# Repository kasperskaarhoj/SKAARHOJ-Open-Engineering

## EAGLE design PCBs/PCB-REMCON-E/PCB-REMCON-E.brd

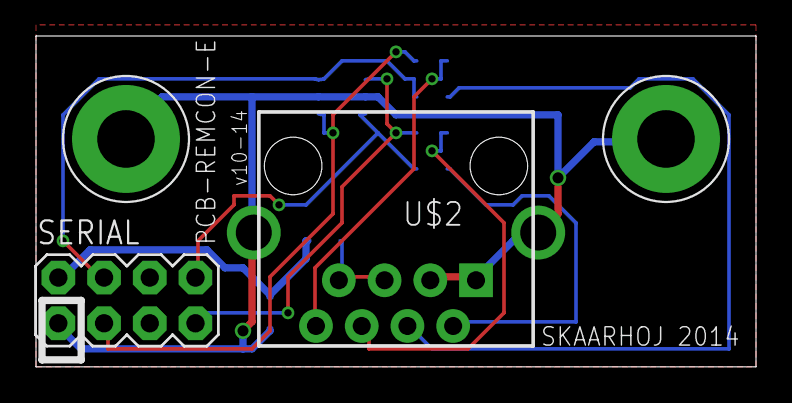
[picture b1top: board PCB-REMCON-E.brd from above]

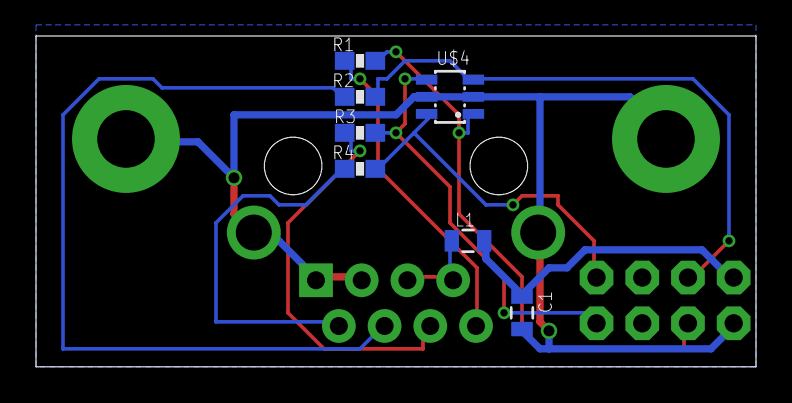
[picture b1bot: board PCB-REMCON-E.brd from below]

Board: 2 copper layers, 40.0 x 18.4 mm, 11 parts (7 on the bottom side), 11 nets.

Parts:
C1: 22uF; 0805
L1: 0805
R1, R2, R3, R4: 50R; 0603-RES
SERIAL: M04X2; 2X4
U$2: RJ45-8_GND
U$3, U$20: GNDPAD6MM; 3.2MMPAD6MM
U$4: TVS_DIODE_ARRAY4; SOT23-6L

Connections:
5V: C1.1, L1.2, SERIAL.2
GND: C1.2, SERIAL.1, U$2.1, U$2.3, U$2.GND, U$2.GND1, U$3.P$1, U$4.2, U$4.5, U$20.P$1
I2C_SCL: R2.2, SERIAL.4, U$4.3
I2C_SCL_IN: R2.1, U$2.4
I2C_SDA: R1.2, SERIAL.3, U$4.1
I2C_SDA_IN: R1.1, U$2.8
unnamed: L1.1, U$2.5, U$2.7
SPI_MOSI: R4.2, SERIAL.8, U$4.6
SPI_MOSI_IN: R4.1, U$2.2
SPI_SCLK: R3.2, SERIAL.7, U$4.4
SPI_SCLK_IN: R3.1, U$2.6

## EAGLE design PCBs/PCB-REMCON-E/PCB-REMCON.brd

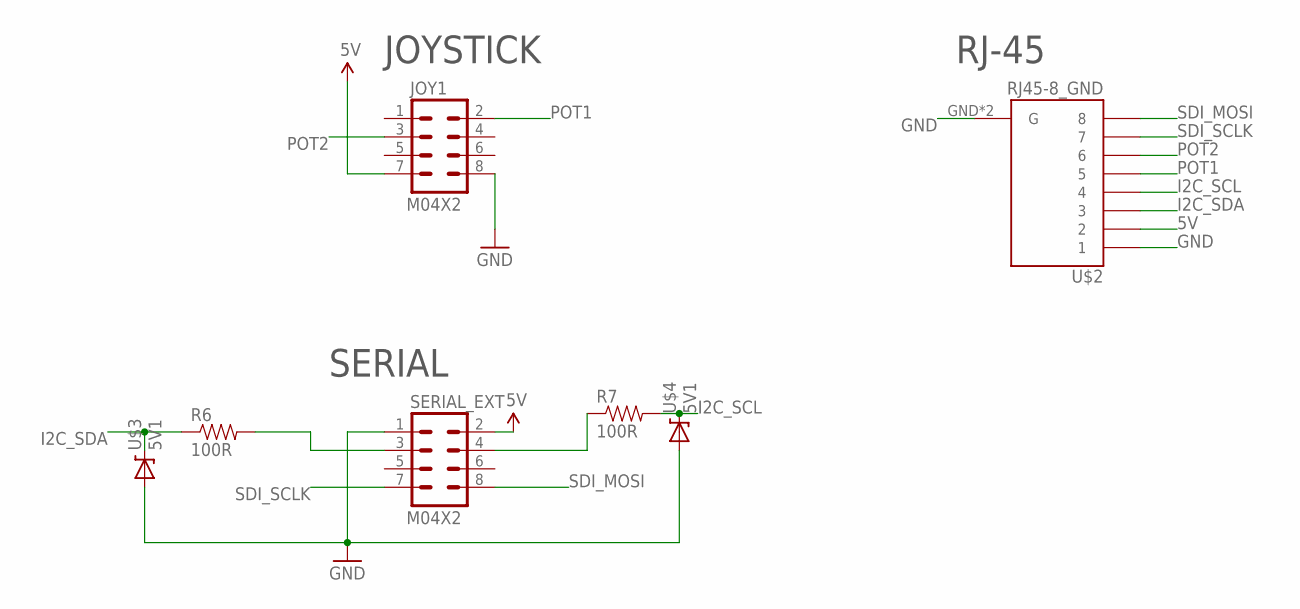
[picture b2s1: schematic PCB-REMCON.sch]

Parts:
JOY1: M04X2; 2X4
R6, R7: 100R; 0603-RES
SERIAL_EXT: M04X2; 2X4
U$2: RJ45-8_GND
U$3, U$4: 5V1; DIODE-ZENER

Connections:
5V: JOY1.7, SERIAL_EXT.2, U$2.2
GND: JOY1.8, SERIAL_EXT.1, U$2.1, U$2.GND (G), U$2.GND1 (G), U$3.P$2 (A), U$4.P$2 (A)
I2C_SCL: R7.2, U$2.4, U$4.P$1 (C)
I2C_SDA: R6.1, U$2.3, U$3.P$1 (C)
unnamed: R6.2, SERIAL_EXT.3
unnamed: R7.1, SERIAL_EXT.4
POT1: JOY1.2, U$2.5
POT2: JOY1.3, U$2.6
SDI_MOSI: SERIAL_EXT.8, U$2.8
SDI_SCLK: SERIAL_EXT.7, U$2.7

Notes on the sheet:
JOYSTICK
SERIAL
RJ-45

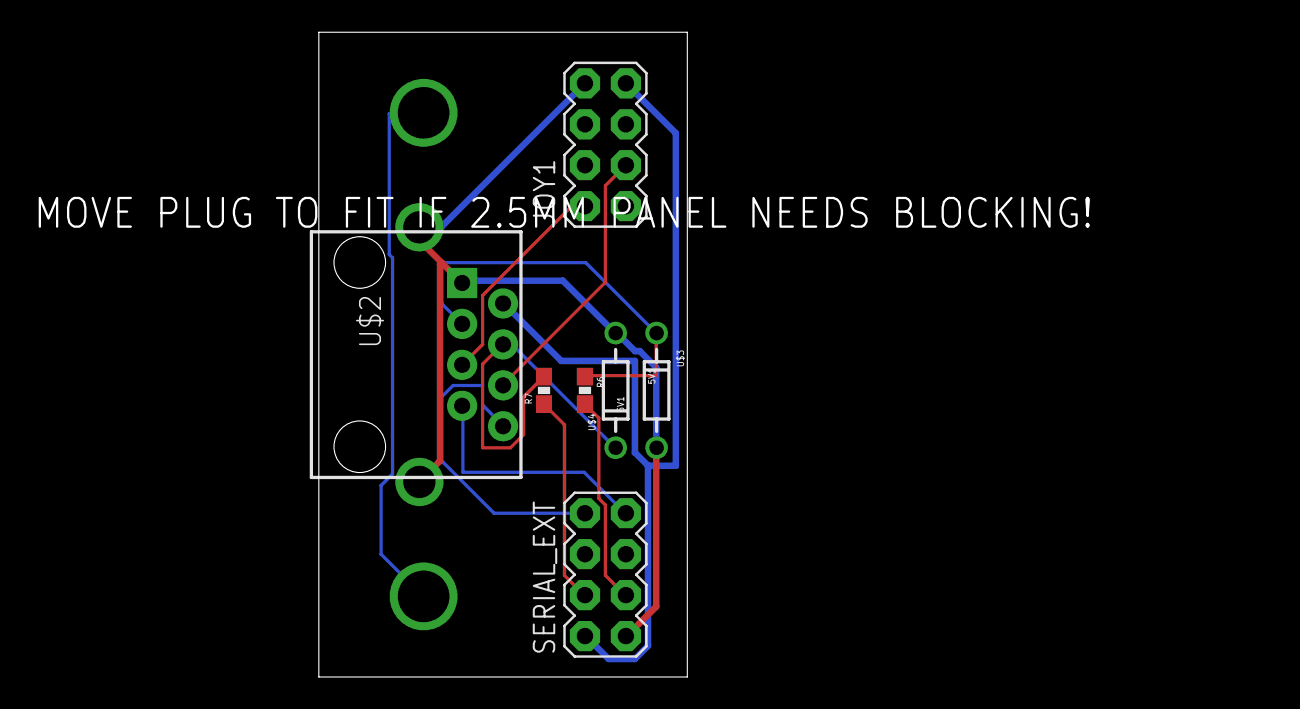
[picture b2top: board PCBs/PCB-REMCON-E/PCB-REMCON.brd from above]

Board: 2 copper layers, 22.9 x 40.0 mm, 7 parts (0 on the bottom side), 10 nets.

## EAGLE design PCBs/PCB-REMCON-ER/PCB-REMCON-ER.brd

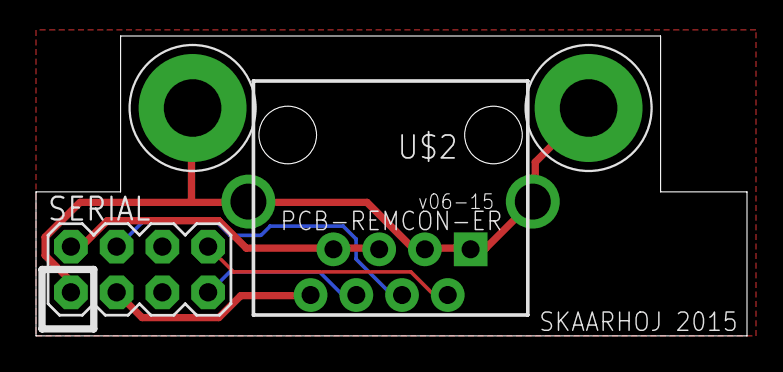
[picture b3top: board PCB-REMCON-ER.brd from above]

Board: 2 copper layers, 39.5 x 16.7 mm, 4 parts (0 on the bottom side), 6 nets.

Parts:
SERIAL: M04X2; 2X4
U$2: RJ45-8_GND
U$3, U$20: GNDPAD6MM; 3.2MMPAD6MM

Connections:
5V: SERIAL.2, U$2.5, U$2.7
GND: SERIAL.1, U$2.1, U$2.3, U$2.GND, U$2.GND1, U$3.P$1, U$20.P$1
I2C_SCL: SERIAL.4, U$2.4
I2C_SDA: SERIAL.3, U$2.8
SDI_MOSI: SERIAL.8, U$2.2
SDI_SCLK: SERIAL.7, U$2.6

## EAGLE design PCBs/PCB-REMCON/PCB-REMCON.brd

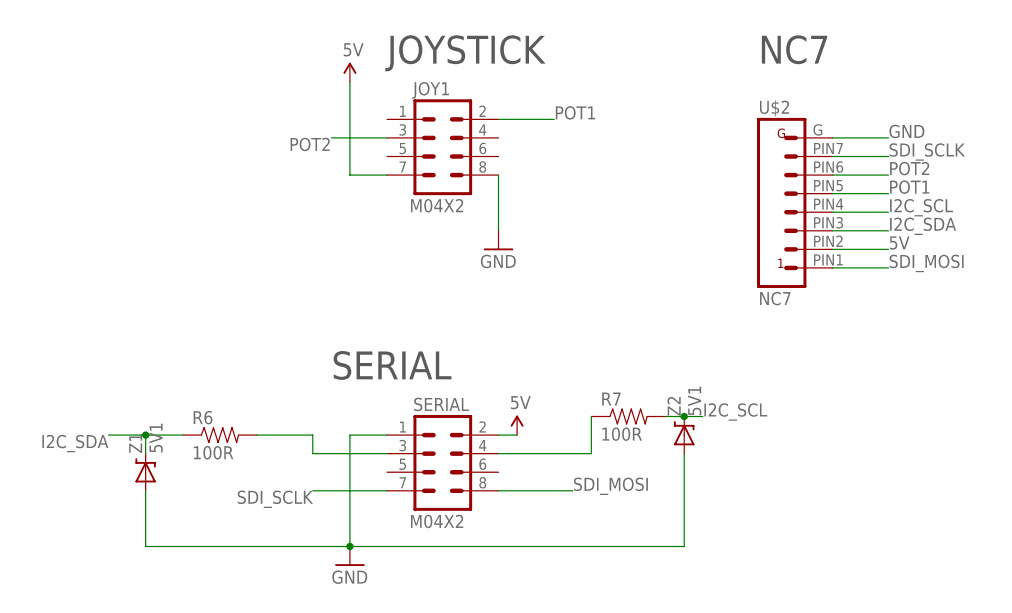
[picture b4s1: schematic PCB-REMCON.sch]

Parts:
JOY1: M04X2; 2X4
R6, R7: 100R; 0603-RES
SERIAL: M04X2; 2X4
U$2: NC7; NC7-MD-L1
Z1, Z2: 5V1; DIODE-ZENER

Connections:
5V: JOY1.7, SERIAL.2, U$2.PIN2 (2)
GND: JOY1.8, SERIAL.1, U$2.G, Z1.P$2 (A), Z2.P$2 (A)
I2C_SCL: R7.2, U$2.PIN4 (4), Z2.P$1 (C)
I2C_SDA: R6.1, U$2.PIN3 (3), Z1.P$1 (C)
unnamed: R6.2, SERIAL.3
unnamed: R7.1, SERIAL.4
POT1: JOY1.2, U$2.PIN5 (5)
POT2: JOY1.3, U$2.PIN6 (6)
SDI_MOSI: SERIAL.8, U$2.PIN1 (1)
SDI_SCLK: SERIAL.7, U$2.PIN7 (7)

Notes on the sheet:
NC7
JOYSTICK
SERIAL

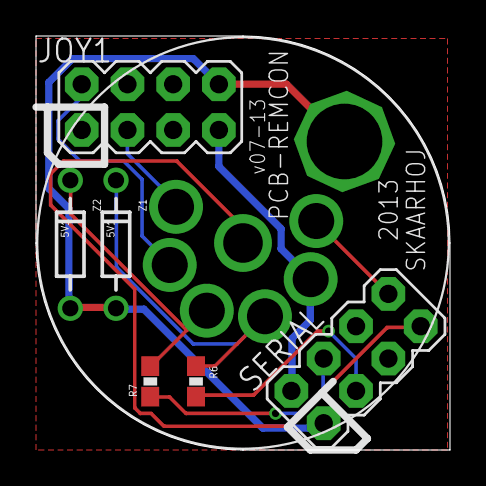
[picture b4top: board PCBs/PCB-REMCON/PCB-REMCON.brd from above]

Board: 2 copper layers, 23.0 x 23.0 mm, 7 parts (0 on the bottom side), 10 nets.

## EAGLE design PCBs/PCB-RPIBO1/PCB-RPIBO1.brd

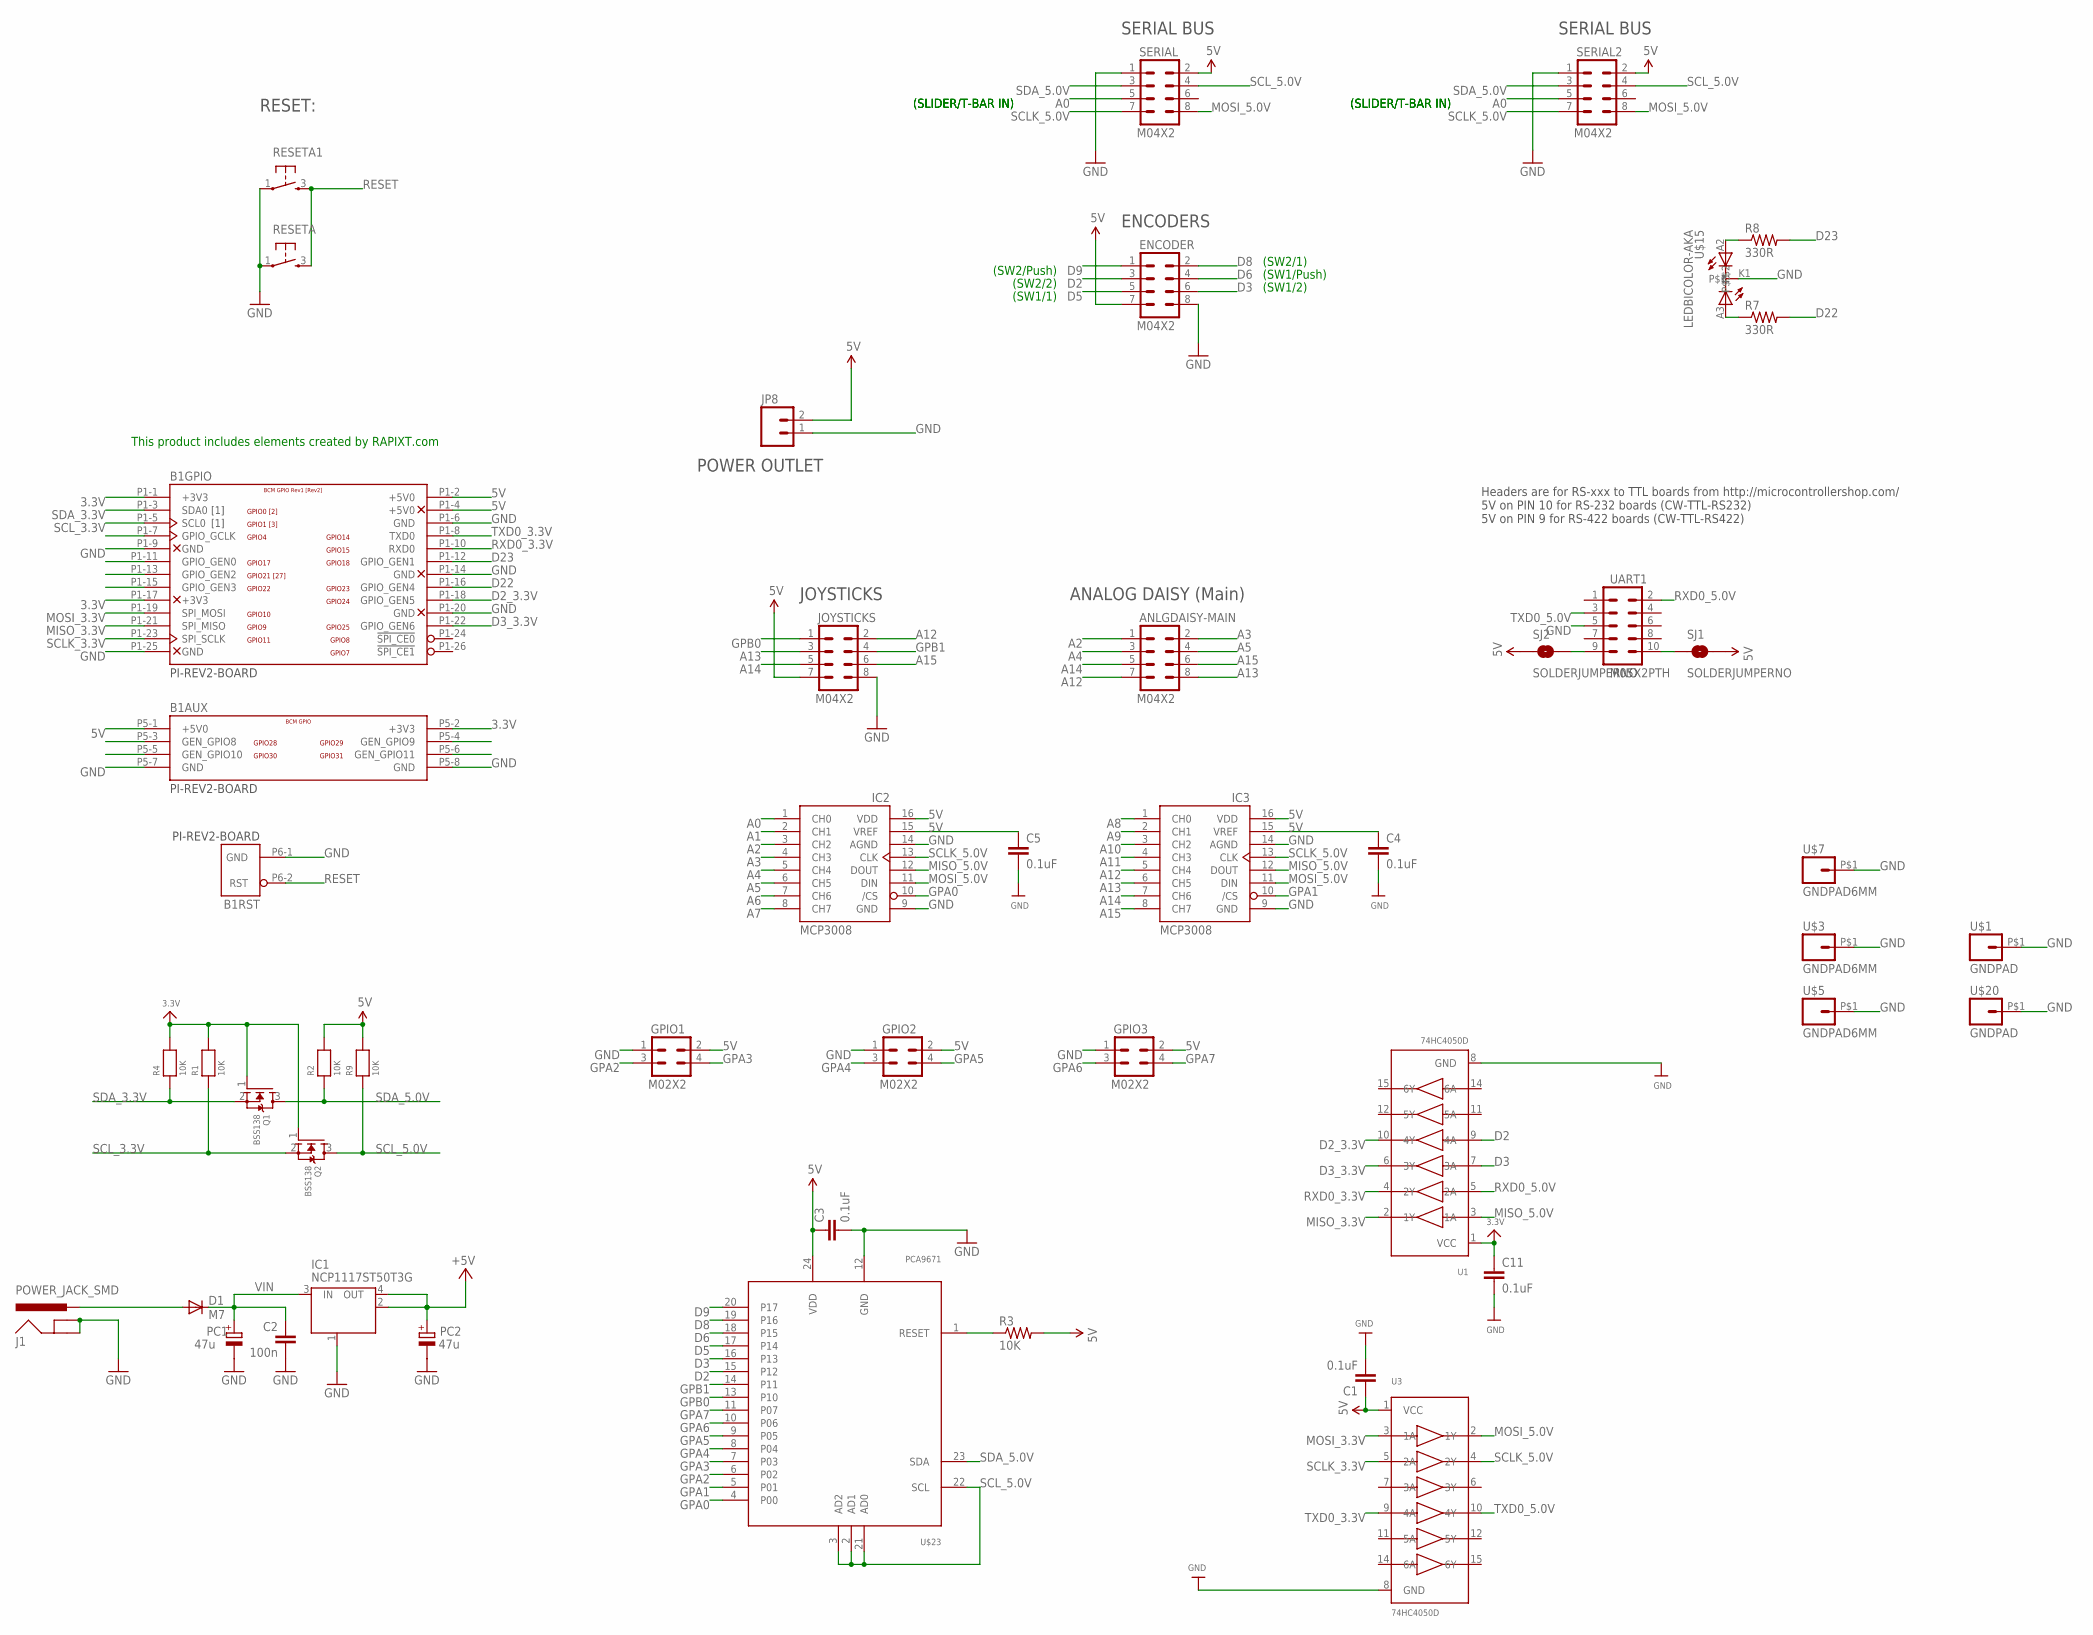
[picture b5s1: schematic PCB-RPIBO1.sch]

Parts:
ANLGDAISY-MAIN: M04X2; 2X4
B1: PI-REV2-BOARD; RASPBERRY-PI-REV2
C1, C3, C4, C5, C11: 0.1uF; 0603-CAP
C2: 100n; C0603-ROUND
D1: M7; SMB
ENCODER: M04X2; 2X4
GPIO1, GPIO2, GPIO3: M02X2; 2X2
IC1: NCP1117ST50T3G; SOT223
IC2, IC3: MCP3008; DIL16
J1: POWER_JACK_SMD
JOYSTICKS: M04X2; 2X4
JP8: M02PTH4; 1X02_XTRA_BIG
PC1, PC2: 47u; PANASONIC_D
Q1, Q2: BSS138; SOT23-WIDE
R1, R2, R4, R9: 10K; 0805
R3: 10K; 0603-RES
R7, R8: 330R; 0603-RES
RESETA, RESETA1: TAC_SWITCH; PUSHBUTTON
SERIAL, SERIAL2: M04X2; 2X4
SJ1, SJ2: SOLDERJUMPERNO; SJ_2S-NO
U1, U3: 74HC4050D; SOIC16
U$1, U$20: GNDPAD; 3.2MMPAD
U$3, U$5, U$7: GNDPAD6MM; 3.2MMPAD6MM
U$15: LEDBICOLOR-AKA; LED5MM-BICOLOR
U$23: PCA9671; TSSOP24
UART1: M05X2PTH; AVR_ICSP

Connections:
3.3V: B1.P1-1 (+3V3), B1.P1-17 (+3V3), B1.P5-2 (+3V3), C11.1, Q1.1 (G), Q2.1 (G), R1.2, R4.2, U1.1 (VCC)
5V: B1.P1-2 (+5V0), B1.P1-4 (+5V0), B1.P5-1 (+5V0), C1.1, C3.1, C4.1, C5.1, ENCODER.7, GPIO1.2, GPIO2.2, GPIO3.2, IC1.2 (OUT), IC1.4 (OUT), IC2.15 (VREF), IC2.16 (VDD), IC3.15 (VREF), IC3.16 (VDD), JOYSTICKS.7, JP8.2, PC2.+, R2.2, R3.2, R9.2, SERIAL.2, SERIAL2.2, SJ1.2, SJ2.1, U3.1 (VCC), U$23.24 (VDD)
12V: D1.A, J1.PWR
A0: IC2.1 (CH0), SERIAL.5, SERIAL2.5
A1: IC2.2 (CH1)
A2: ANLGDAISY-MAIN.1, IC2.3 (CH2)
A3: ANLGDAISY-MAIN.2, IC2.4 (CH3)
A4: ANLGDAISY-MAIN.3, IC2.5 (CH4)
A5: ANLGDAISY-MAIN.4, IC2.6 (CH5)
A6: IC2.7 (CH6)
A7: IC2.8 (CH7)
A8: IC3.1 (CH0)
A9: IC3.2 (CH1)
A10: IC3.3 (CH2)
A11: IC3.4 (CH3)
A12: ANLGDAISY-MAIN.7, IC3.5 (CH4), JOYSTICKS.2
A13: ANLGDAISY-MAIN.8, IC3.6 (CH5), JOYSTICKS.3
A14: ANLGDAISY-MAIN.5, IC3.7 (CH6), JOYSTICKS.5
A15: ANLGDAISY-MAIN.6, IC3.8 (CH7), JOYSTICKS.6
D2: ENCODER.3, U1.9 (4A), U$23.15 (P12)
D2_3.3V: B1.P1-18 (GPIO_GEN5), U1.10 (4Y)
D3: ENCODER.6, U1.7 (3A), U$23.16 (P13)
D3_3.3V: B1.P1-22 (GPIO_GEN6), U1.6 (3Y)
D5: ENCODER.5, U$23.17 (P14)
D6: ENCODER.4, U$23.18 (P15)
D8: ENCODER.2, U$23.19 (P16)
D9: ENCODER.1, U$23.20 (P17)
D22: B1.P1-16 (GPIO_GEN4), R7.2
D23: B1.P1-12 (GPIO_GEN1), R8.2
GND: B1.P1-6 (GND), B1.P1-9 (GND), B1.P1-14 (GND), B1.P1-20 (GND), B1.P1-25 (GND), B1.P5-7 (GND), B1.P5-8 (GND), B1.P6-1 (GND), C1.2, C2.2, C3.2, C4.2, C5.2, C11.2, ENCODER.8, GPIO1.1, GPIO2.1, GPIO3.1, IC1.1 (GND/ADJ), IC2.9 (GND), IC2.14 (AGND), IC3.9 (GND), IC3.14 (AGND), J1.GND, J1.SHUNT (GNDBREAK), JOYSTICKS.8, JP8.1, PC1.-, PC2.-, RESETA.1, RESETA1.1, SERIAL.1, SERIAL2.1, U1.8 (GND), U3.8 (GND), U$1.P$1, U$3.P$1, U$5.P$1, U$7.P$1, U$15.K1, U$20.P$1, U$23.12 (GND), UART1.5
GPA0: IC2.10 (/CS), U$23.4 (P00)
GPA1: IC3.10 (/CS), U$23.5 (P01)
GPA2: GPIO1.3, U$23.6 (P02)
GPA3: GPIO1.4, U$23.7 (P03)
GPA4: GPIO2.3, U$23.8 (P04)
GPA5: GPIO2.4, U$23.9 (P05)
GPA6: GPIO3.3, U$23.10 (P06)
GPA7: GPIO3.4, U$23.11 (P07)
GPB0: JOYSTICKS.1, U$23.13 (P10)
GPB1: JOYSTICKS.4, U$23.14 (P11)
MISO_3.3V: B1.P1-21 (SPI_MISO), U1.2 (1Y)
MISO_5.0V: IC2.12 (DOUT), IC3.12 (DOUT), U1.3 (1A)
MOSI_3.3V: B1.P1-19 (SPI_MOSI), U3.3 (1A)
MOSI_5.0V: IC2.11 (DIN), IC3.11 (DIN), SERIAL.8, SERIAL2.8, U3.2 (1Y)
unnamed: R3.1, U$23.1 (RESET)
unnamed: SJ2.2, UART1.9
unnamed: SJ1.1, UART1.10
unnamed: R8.1, U$15.A2
unnamed: R7.1, U$15.A3
RESET: B1.P6-2 (RST), RESETA.3, RESETA1.3
RXD0_3.3V: B1.P1-10 (RXD0), U1.4 (2Y)
RXD0_5.0V: U1.5 (2A), UART1.2
SCLK_3.3V: B1.P1-23 (SPI_SCLK), U3.5 (2A)
SCLK_5.0V: IC2.13 (CLK), IC3.13 (CLK), SERIAL.7, SERIAL2.7, U3.4 (2Y)
SCL_3.3V: B1.P1-5 (SCL0), Q2.2 (S), R1.1
SCL_5.0V: Q2.3 (D), R9.1, SERIAL.4, SERIAL2.4, U$23.2 (AD1), U$23.3 (AD2), U$23.21 (AD0), U$23.22 (SCL)
SDA_3.3V: B1.P1-3 (SDA0), Q1.2 (S), R4.1
SDA_5.0V: Q1.3 (D), R2.1, SERIAL.3, SERIAL2.3, U$23.23 (SDA)
TXD0_3.3V: B1.P1-8 (TXD0), U3.9 (4A)
TXD0_5.0V: U3.10 (4Y), UART1.3
VIN: C2.1, D1.C, IC1.3 (IN), PC1.+

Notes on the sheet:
JOYSTICKS
Headers are for RS-xxx to TTL boards from http://microcontrollershop.com/ 5V on PIN 10 for RS-232 boards (CW-TTL-RS232) 5V on PIN 9 for RS-422 boards (CW-TTL-RS422)
ENCODERS
SERIAL BUS
(SLIDER/T-BAR IN)
(SW2/Push)
(SW2/2)
(SW1/1)
(SW2/1)
(SW1/Push)
(SW1/2)
RESET:
ANALOG DAISY (Main)
POWER OUTLET
This product includes elements created by RAPIXT.com

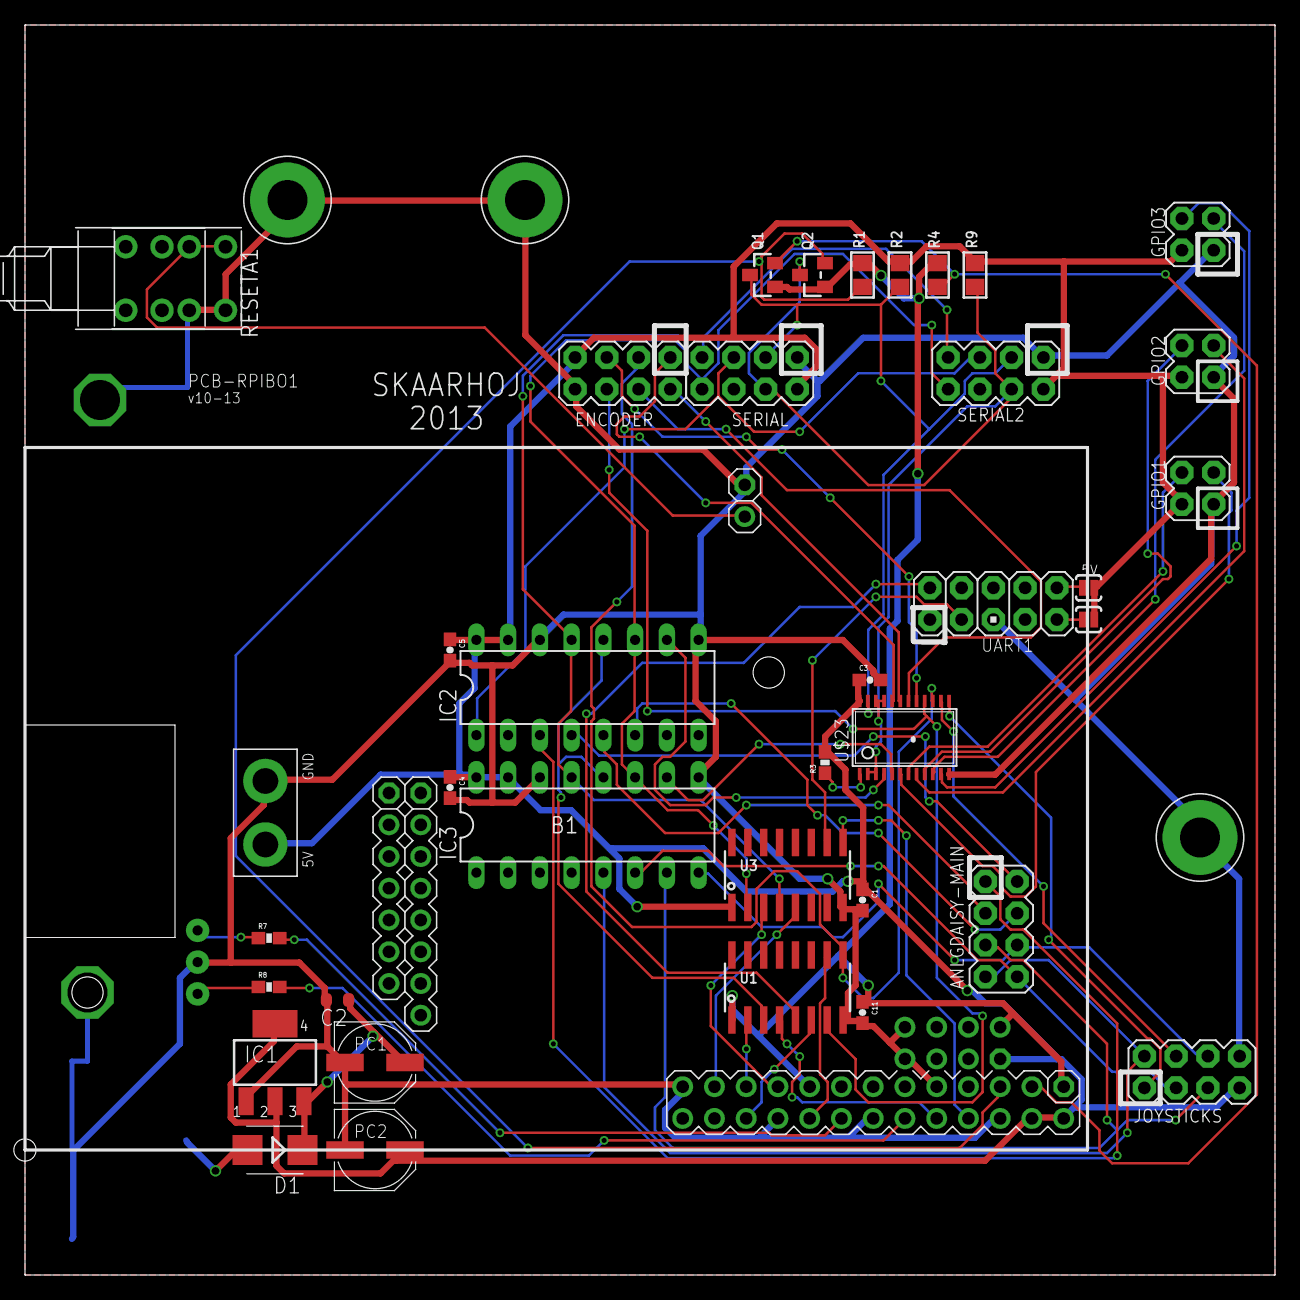
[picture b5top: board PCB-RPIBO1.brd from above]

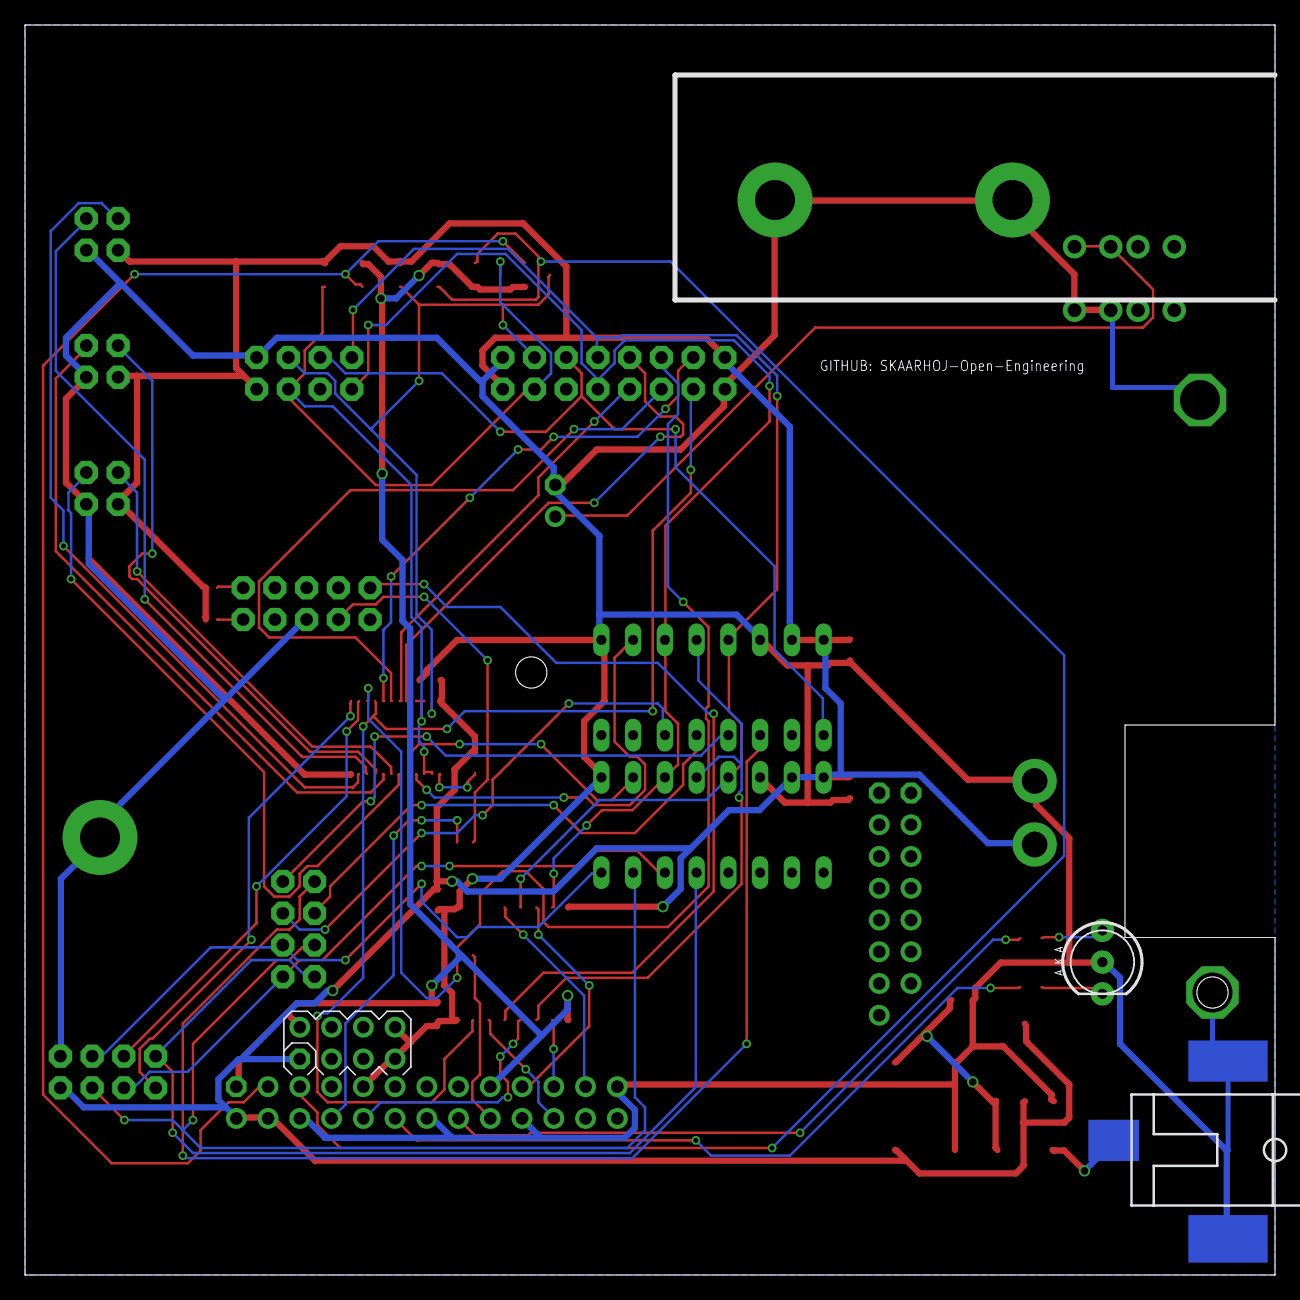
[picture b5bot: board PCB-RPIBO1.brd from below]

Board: 2 copper layers, 100.0 x 100.0 mm, 46 parts (2 on the bottom side), 54 nets.

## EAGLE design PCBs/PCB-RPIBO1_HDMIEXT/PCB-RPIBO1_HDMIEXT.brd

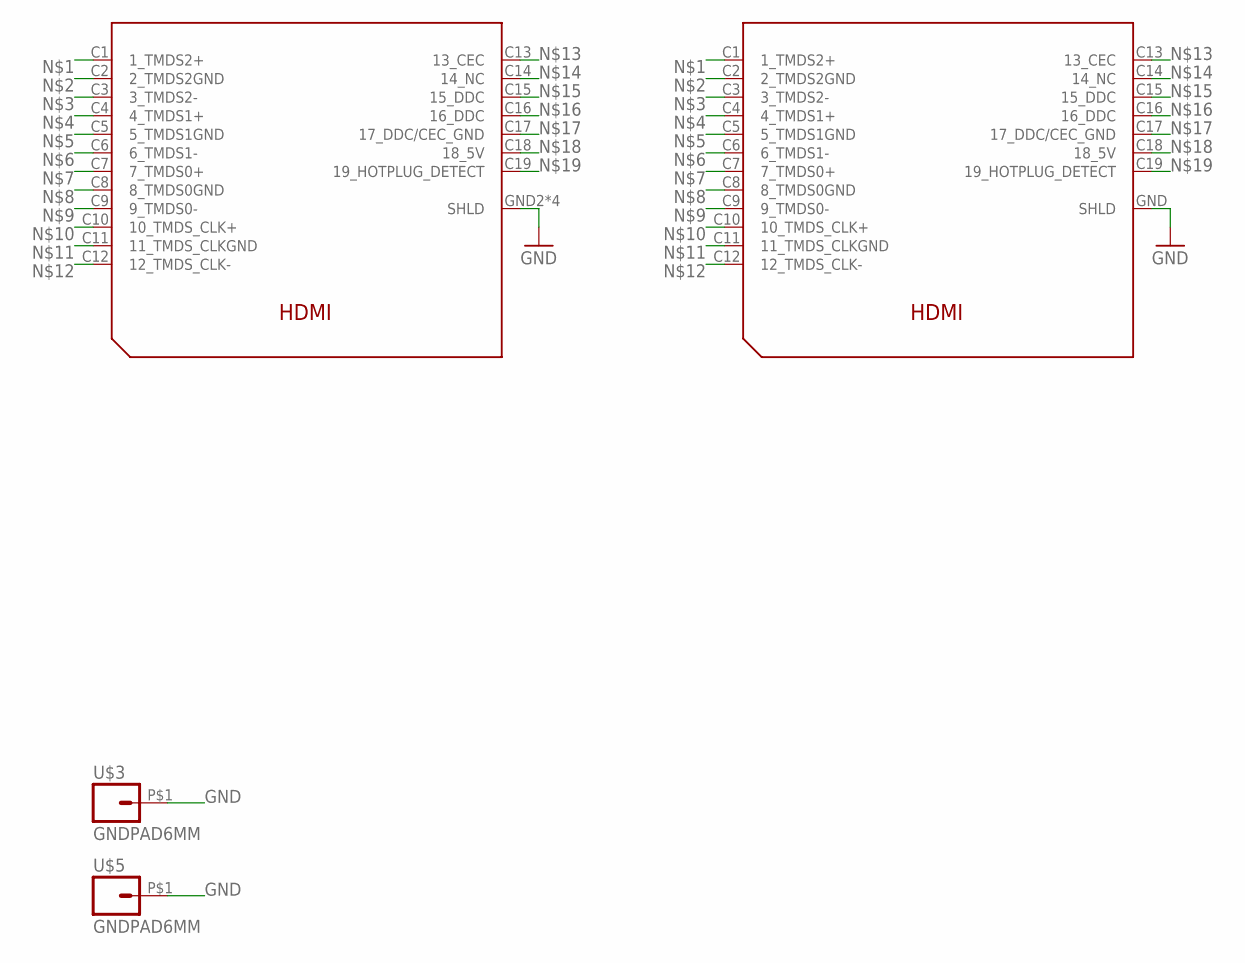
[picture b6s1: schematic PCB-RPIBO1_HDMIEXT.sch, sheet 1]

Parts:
U$1: HDMI
U$2: HDMIPCBMALECON; HDMI_MALEINTERCON
U$3, U$5: GNDPAD6MM; 3.2MMPAD6MM

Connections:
GND: U$1.GND2 (SHLD), U$1.GND3 (SHLD), U$1.P$2 (SHLD), U$1.P$3 (SHLD), U$2.GND (SHLD), U$3.P$1, U$5.P$1
unnamed: U$1.C1 (1_TMDS2+), U$2.C1 (1_TMDS2+)
unnamed: U$1.C2 (2_TMDS2GND), U$2.C2 (2_TMDS2GND)
unnamed: U$1.C3 (3_TMDS2-), U$2.C3 (3_TMDS2-)
unnamed: U$1.C4 (4_TMDS1+), U$2.C4 (4_TMDS1+)
unnamed: U$1.C5 (5_TMDS1GND), U$2.C5 (5_TMDS1GND)
unnamed: U$1.C6 (6_TMDS1-), U$2.C6 (6_TMDS1-)
unnamed: U$1.C7 (7_TMDS0+), U$2.C7 (7_TMDS0+)
unnamed: U$1.C8 (8_TMDS0GND), U$2.C8 (8_TMDS0GND)
unnamed: U$1.C9 (9_TMDS0-), U$2.C9 (9_TMDS0-)
unnamed: U$1.C10 (10_TMDS_CLK+), U$2.C10 (10_TMDS_CLK+)
unnamed: U$1.C11 (11_TMDS_CLKGND), U$2.C11 (11_TMDS_CLKGND)
unnamed: U$1.C12 (12_TMDS_CLK-), U$2.C12 (12_TMDS_CLK-)
unnamed: U$1.C13 (13_CEC), U$2.C13 (13_CEC)
unnamed: U$1.C14 (14_NC), U$2.C14 (14_NC)
unnamed: U$1.C15 (15_DDC), U$2.C15 (15_DDC)
unnamed: U$1.C16 (16_DDC), U$2.C16 (16_DDC)
unnamed: U$1.C17 (17_DDC/CEC_GND), U$2.C17 (17_DDC/CEC_GND)
unnamed: U$1.C18 (18_5V), U$2.C18 (18_5V)
unnamed: U$1.C19 (19_HOTPLUG_DETECT), U$2.C19 (19_HOTPLUG_DETECT)

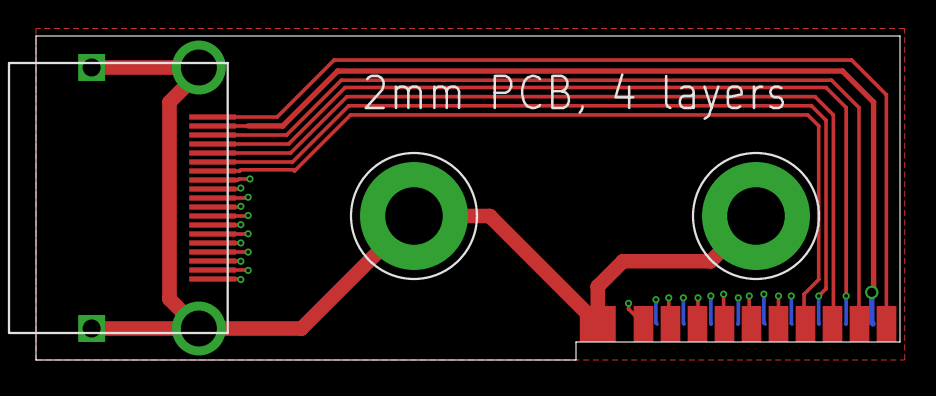
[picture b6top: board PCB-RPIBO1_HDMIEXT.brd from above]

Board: 4 copper layers, 48.0 x 18.0 mm, 4 parts (0 on the bottom side), 20 nets.

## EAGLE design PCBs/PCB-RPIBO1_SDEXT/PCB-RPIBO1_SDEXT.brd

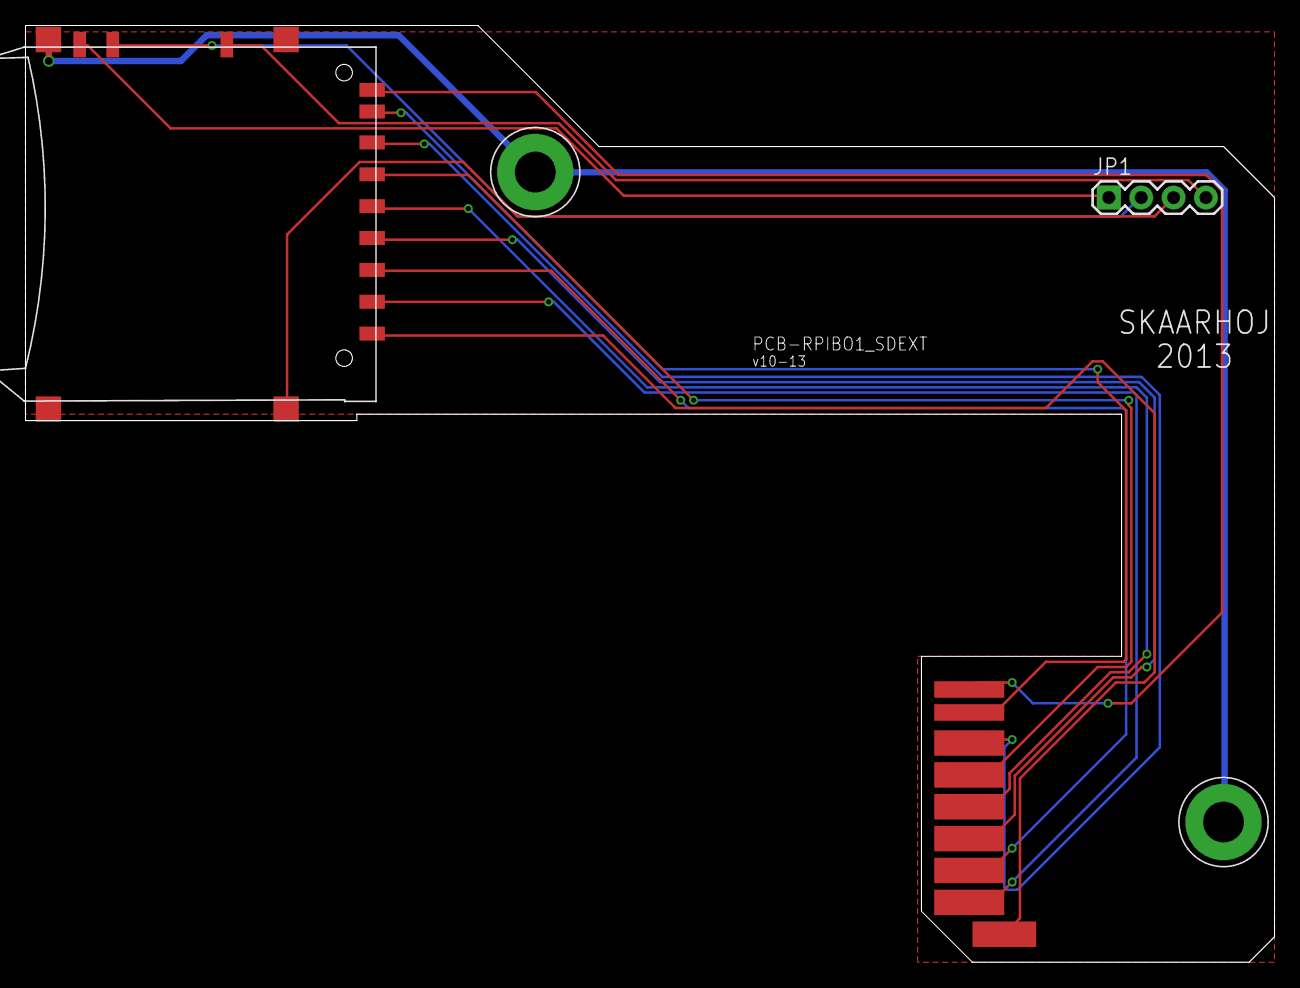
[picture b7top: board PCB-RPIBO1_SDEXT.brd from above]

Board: 2 copper layers, 98.0 x 73.5 mm, 5 parts (1 on the bottom side), 14 nets.

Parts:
JP1: 1X04
U$2: SD06132; SD_LARGE
U$4: SDMALEPCB; SD_MALEPCB
U$5, U$7: GNDPAD6MM; 3.2MMPAD6MM

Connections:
GND: U$2.GP, U$5.P$1, U$7.P$1
unnamed: U$2.7, U$4.7
unnamed: U$2.2, U$4.2
unnamed: U$2.5, U$4.5
unnamed: U$2.1, U$4.1
unnamed: U$2.8, U$4.8
unnamed: U$2.9, U$4.9
unnamed: JP1.4, U$2.CD
unnamed: JP1.3, U$2.GP3
unnamed: JP1.2, U$2.WP
unnamed: JP1.1, U$2.WP1
VDD: U$2.4, U$4.4
VSS1: U$2.3, U$4.3
VSS2: U$2.6, U$4.6

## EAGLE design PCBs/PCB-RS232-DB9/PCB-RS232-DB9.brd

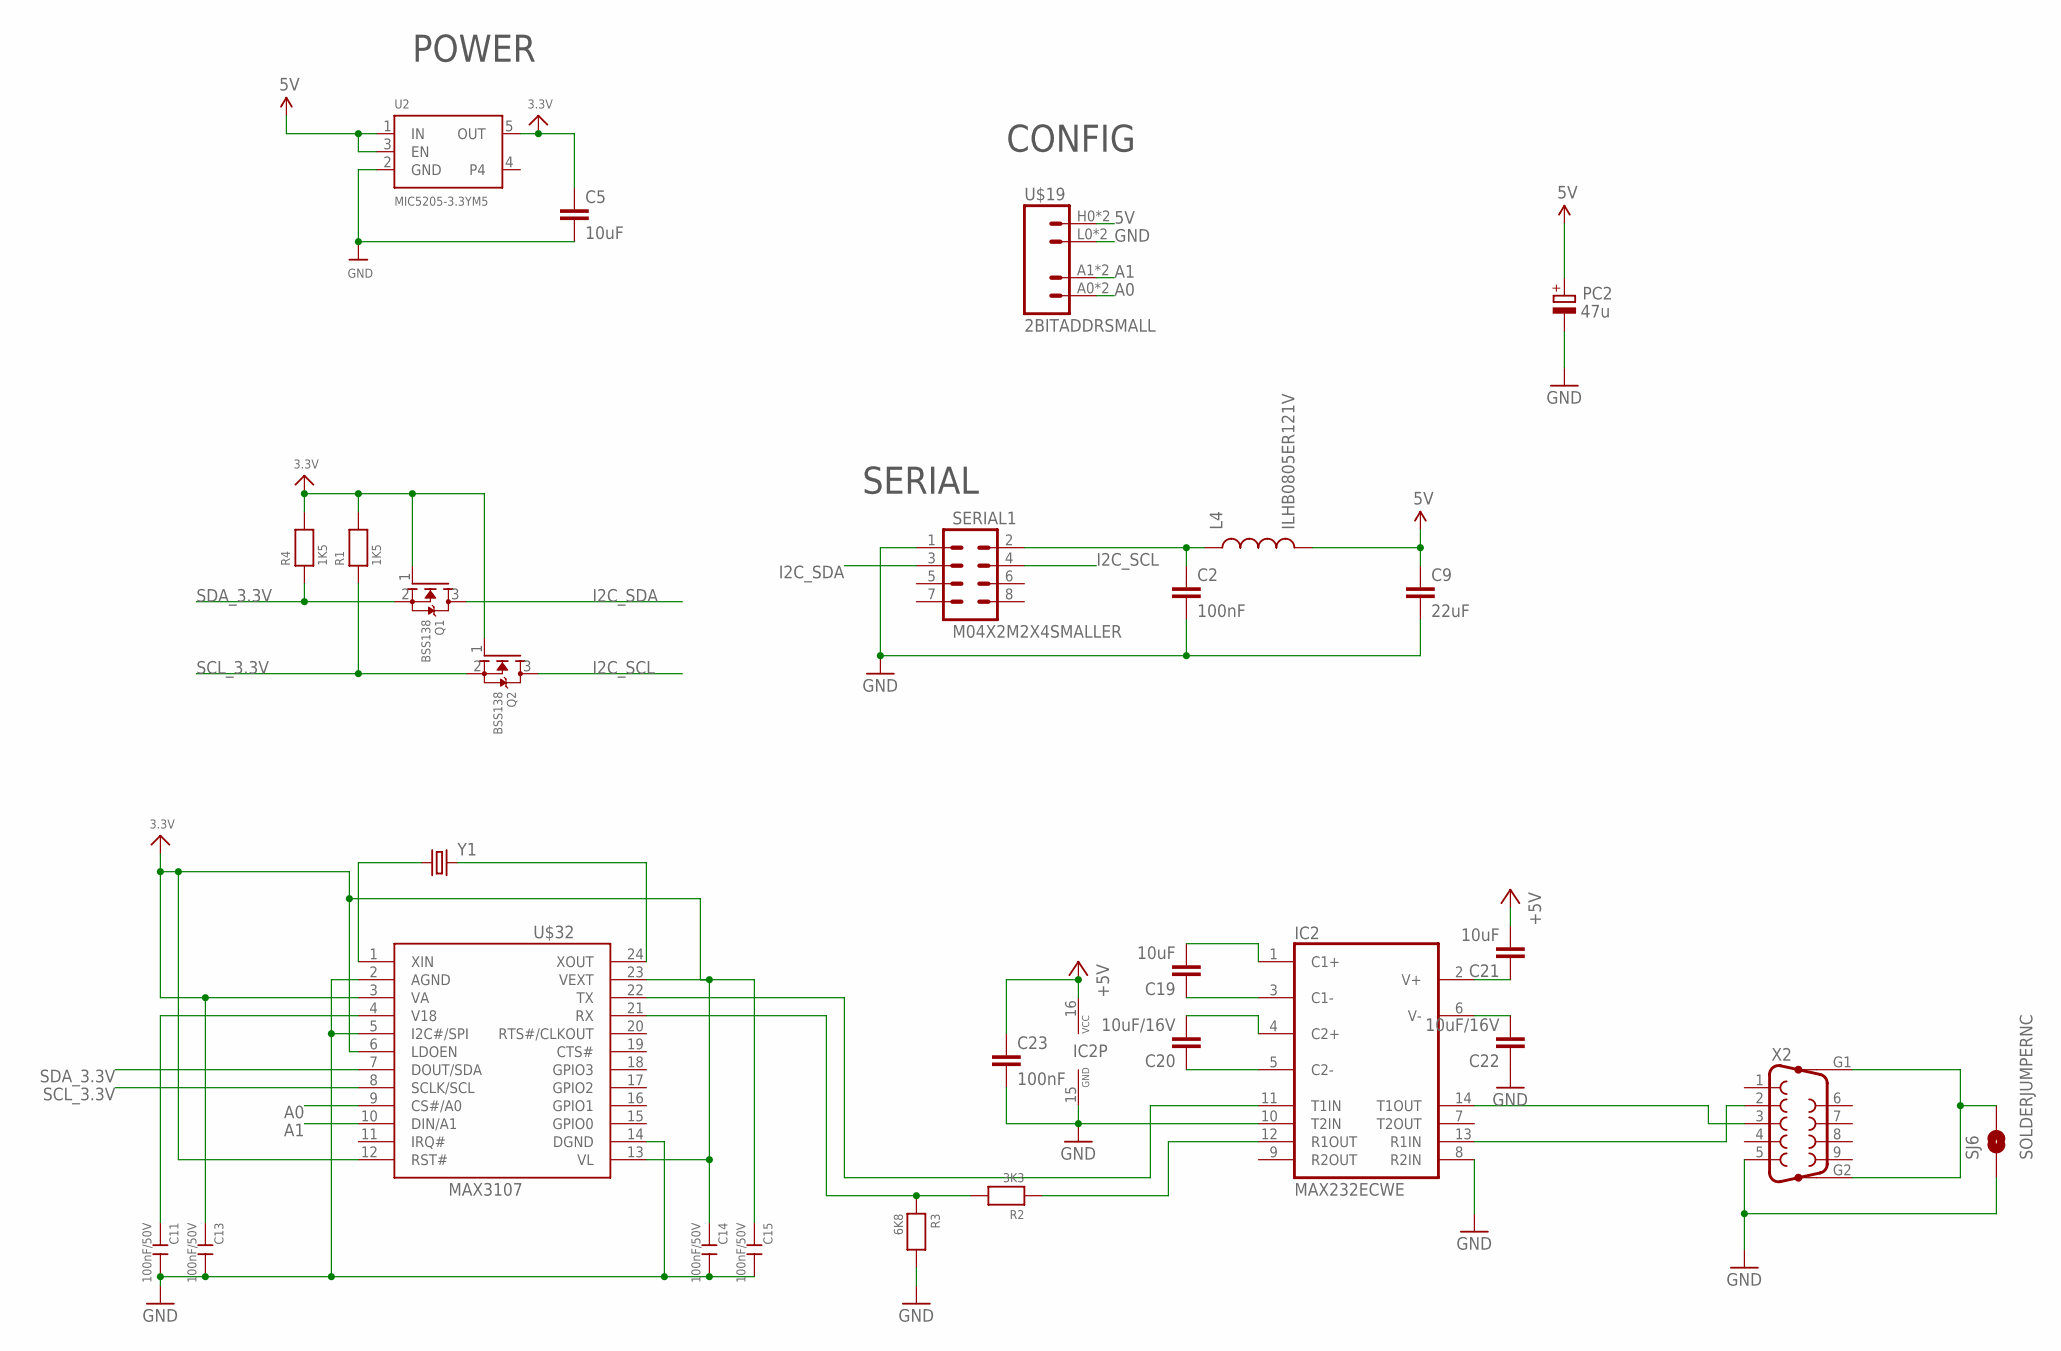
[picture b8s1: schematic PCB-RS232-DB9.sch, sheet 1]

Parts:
C2, C23: 100nF; 0603-CAP
C5, C19, C21: 10uF; 0805
C9: 22uF; 0805
C11, C13, C14, C15: 100nF/50V; C0603
C20, C22: 10uF/16V; 0805
IC2: MAX232ECWE; SO16L
L4: ILHB0805ER121V; 0805
PC2: 47u; PANASONIC_D
Q1, Q2: BSS138; SOT23-R
R1, R4: 1K5; 0603
R2: 3K3; 0603
R3: 6K8; 0603
SERIAL1: M04X2M2X4SMALLER; M2X4SMALLER
SJ6: SOLDERJUMPERNC; SJ_2S
U2: MIC5205-3.3YM5; SOT23-5
U$19: 2BITADDRSMALL; 2BITADDR_SMALL
U$32: MAX3107; SSOP24
X2: F09HP
Y1: CRYSTALHC49US; HC49US

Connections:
3.3V: C5.1, C13.1, C14.1, C15.1, Q1.1 (G), Q2.1 (G), R1.2, R4.2, U2.5 (OUT), U$32.3 (VA), U$32.6 (LDOEN), U$32.12 (RST#), U$32.13 (VL), U$32.23 (VEXT)
5V: C9.1, C21.2, C23.1, IC2.16 (VCC), L4.2, PC2.+, U2.1 (IN), U2.3 (EN), U$19.H0 (VCC), U$19.H1 (VCC)
A0: U$19.A0 (A1), U$19.AS0 (A1), U$32.9 (CS#/A0)
A1: U$19.A1 (A2), U$19.AS1 (A2), U$32.10 (DIN/A1)
GND: C2.2, C5.2, C9.2, C11.2, C13.2, C14.2, C15.2, C22.1, C23.2, IC2.8 (R2IN), IC2.10 (T2IN), IC2.15 (GND), PC2.-, R3.2, SERIAL1.1, SJ6.1, U2.2 (GND), U$19.L0 (GND), U$19.L1 (GND), U$32.2 (AGND), U$32.5 (I2C#/SPI), U$32.14 (DGND), X2.5
I2C_SCL: Q2.3 (D), SERIAL1.4
I2C_SDA: Q1.3 (D), SERIAL1.3
MAX232_V+: C21.1, IC2.2 (V+)
unnamed: IC2.11 (T1IN), U$32.22 (TX)
unnamed: R2.2, R3.1, U$32.21 (RX)
unnamed: C2.1, L4.1, SERIAL1.2
unnamed: C19.1, IC2.3 (C1-)
unnamed: C20.1, IC2.5 (C2-)
unnamed: C11.1, U$32.4 (V18)
unnamed: C20.2, IC2.4 (C2+)
unnamed: IC2.12 (R1OUT), R2.1
unnamed: SJ6.2, X2.G1, X2.G2
unnamed: U$32.1 (XIN), Y1.1
unnamed: IC2.13 (R1IN), X2.2
unnamed: IC2.14 (T1OUT), X2.3
unnamed: U$32.24 (XOUT), Y1.2
unnamed: C19.2, IC2.1 (C1+)
unnamed: C22.2, IC2.6 (V-)
SCL_3.3V: Q2.2 (S), R1.1, U$32.8 (SCLK/SCL)
SDA_3.3V: Q1.2 (S), R4.1, U$32.7 (DOUT/SDA)

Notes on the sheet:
SERIAL
POWER
CONFIG

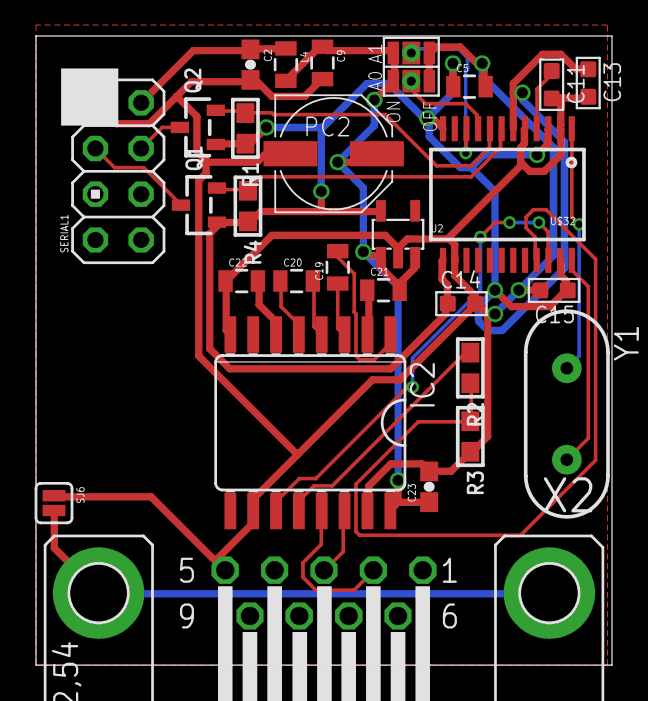
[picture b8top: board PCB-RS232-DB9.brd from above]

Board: 2 copper layers, 32.0 x 35.0 mm, 28 parts (0 on the bottom side), 25 nets.

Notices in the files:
parts and their libraries:
SparkFun: Licensing: CC v3.0 Share-Alike You are welcome to use this library for commercial purposes.
